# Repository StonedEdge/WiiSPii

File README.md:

# The Wii SPii (A custom GBA SP themed portable gaming console) 

## Description
The Wii SPii is an open source, portable Wii project by StonedEdge from the BitBuilt forums. It uses real Wii hardware with no emulation and lasts around 2.5 hours on a full charge. This repository includes includes code from several contributors to the hobby (Aurelio, Gmanmodz and Jefflongo), 
CAD files, gerbers for main PCB ordering and a BOM of parts for assembly. I plan to include a guide for assembly here at a later stage. The main build worklog can be found [here:](https://bitbuilt.net/forums/index.php?threads/the-wii-spii.3347/)

### Code 
The code used in this project is based on the RVL-PMS (Gman), GC+ 2.0 (Aurelio92) and STUSB4500 (jefflongo) source code from below contributors, with minor tweaks being made to suit my project needs. All credit goes to contributors and I take no credit in their work whatsoever, I simply took their contributions and made slight changes. The project code is in the form of an MPLAB X project and can be compiled using MPLAB X IDE with XC8 compiler. Alternatively, you can also use the pre-compiled program (.hex) to program the PIC16LF15324, PIC16F15324 and PIC18F25K42 with MPLAB IPE. The microcontrollers were programmed using a PICKit 3. The only code that you will need to adjust and then compile is the lines 71-74 Lmin, Lmax, Rmin and Rmax values in config.c, in order to scale the analog triggers to the correct values after reading the initial ADC values when the triggers are depressed and pressed. Code is located in the zip files. 

### CAD
The CAD files for the Wii SPii project can be found here. The case was designed with CNC manufacturing in mind and can be machined with little issue. I may include the toolpathing files at a later date, but have decided not to for now. I have uploaded both the .STEP and .STL files so that people may easily make changes to the model in their CAD software of choice, or simply print the case on any 3D printer. Prototypes were made on the Prusa i3 MK3s FDM printer and the final design was completed on a 3-axis CNC machine in acrylic plastic. I will not be taking any requests for CNC cases. 

### PCB
The PCB is a 4 layer PCB ordered from JLCPCB. The PCB can also be ordered from OSHPark or PCBway, however due to increased cost for 4-layer PCB, I would recommend ordering directly from JLCPCB for quick turnaround. A stencil is also required for ease of assembly along with solder paste and hot air to assemble the boards. I made a 3D printable stencil jig that can be used for easy placement of the stencil and PCB that I have included within the CAD zip files above. 

### BOM (Bill of Materials) 
These are the required components you will need to build the Wii SPii. This includes the PCB itself, PCB components and other peripherals required to make the console. It can be found [here:](xxx)

### Contributors 
I'd like to thank these people in no particular order for the awesome work you have done to help me complete this project. A link to their GitHub repositories can be found below. 

* Dmcke5 for helping me re-model the WiiSPii for CNC machining, CNC machining the case out of acrylic and of course the hours and hours of phone calls back and forth over the past few months. Thanks for putting up with my numerous questions on CNC
* [Gman](https://github.com/Gmanmodz) for providing the community with countless hours of research and sharing his code to allow me to make some small modifications to the LED interface and audio amplifier
* [Aurelio](https://github.com/Aurelio92) for GC+ 2.0 and BBloader Wii GUI contributions and updates
* robertlong13 for assisting in the PIC16LF15324 ADC modifications for using 10K pot for volume control over i2c
* [JeffLongo](https://github.com/jefflongo) for his STUSB4500 code revisions 
* YveltalGriffin for suggesting various hardware changes and reviews to PCB/schematics

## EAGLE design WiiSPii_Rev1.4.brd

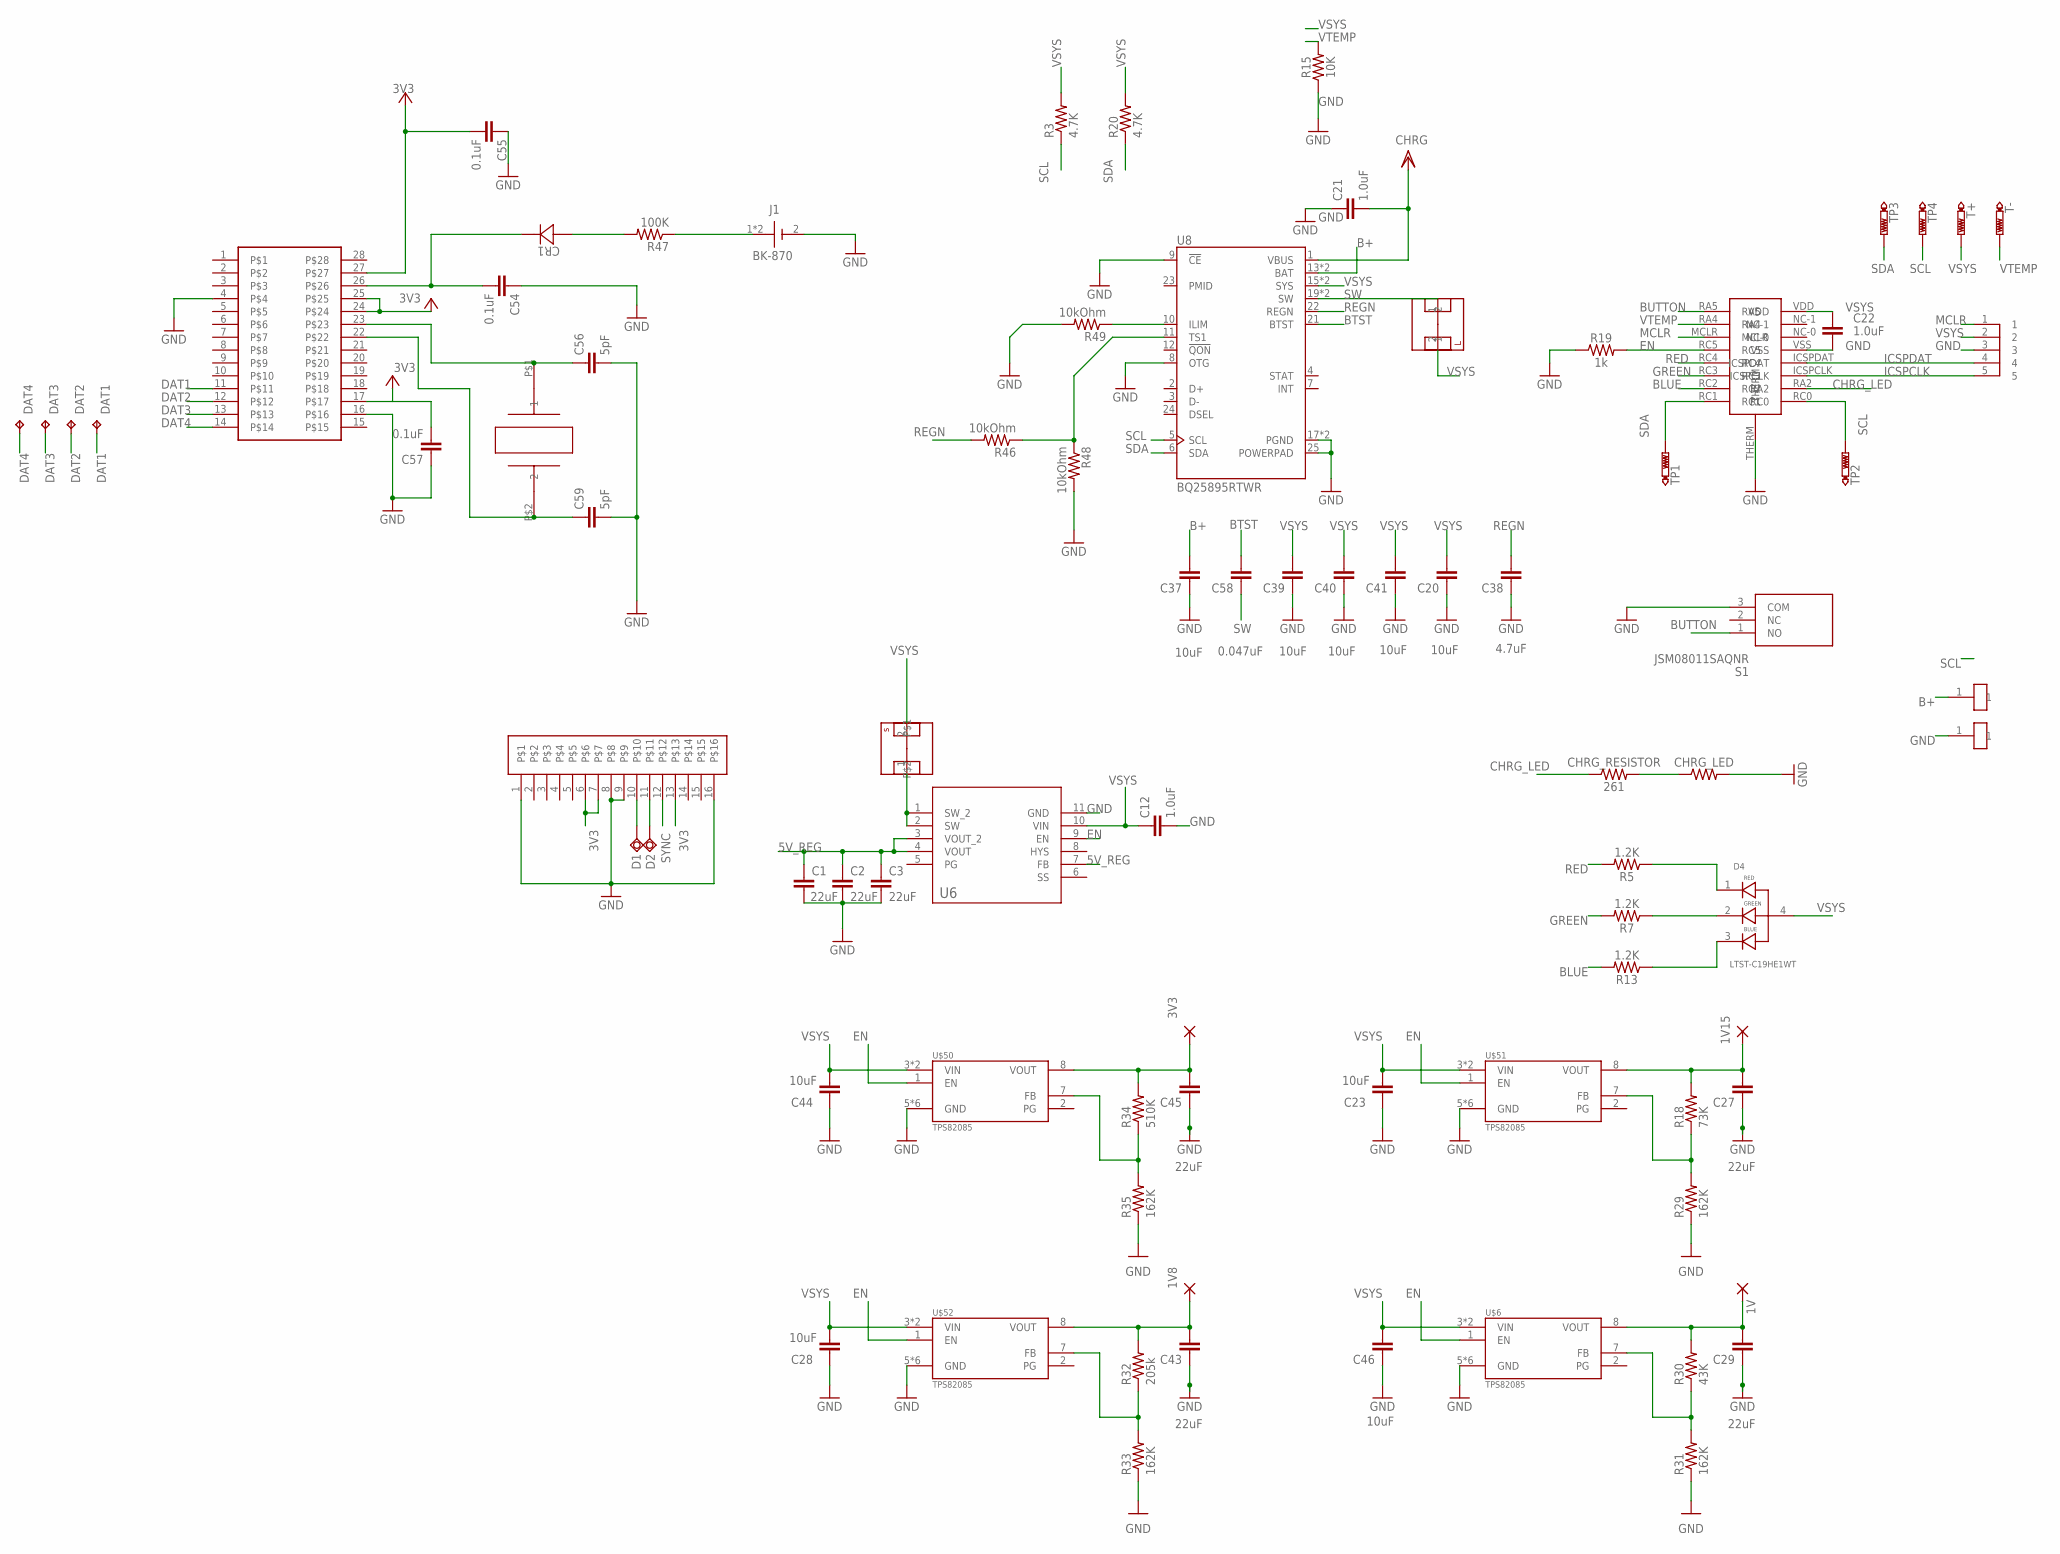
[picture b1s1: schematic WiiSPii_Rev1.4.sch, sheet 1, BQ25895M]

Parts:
1V, 1V8, 1V15, 3V3: SMD2; SMD1,27-2,54
BT_DATA1, BT_DATA2: TPSQB1,27; B1,27
C1, C2, C3, C27, C29, C43, C45: 22uF; 0805
C12, C21, C22: 1.0uF; 0805
C20, C23, C28, C37, C39, C40, C41, C44, C46: 10uF; 0805
C38: 4.7uF; C0402
C54, C55, C57: 0.1uF; C0402
C56, C59: 5pF; C0402
C58: 0.047uF; C0402
CHRG_LED: 261; 0603
CHRG_RESISTOR: 261; 0603
CR1: BAT60JFILM; SOD-323_STM
D4: LTST-C19HE1WT; LED_LTST-C19HE1WT
DAT1, DAT2, DAT3, DAT4: TPB1,27; B1,27
J1: BK-870; MPD_BK-870
R3, R20: 4.7K; R0402
R5, R7, R13: 1.2K; 0603
R15: 10K; 0603
R18: 73K; R0402
R19: 1k; 0603
R29, R31, R33, R35: 162K; R0402
R30: 43K; R0402
R32: 205k; R0402
R34: 510K; R0402
R46, R48, R49: 10kOhm; R0402
R47: 100K; R0402
S1: JSM08011SAQNR
T+: PTR1TP09R; TP09R
T-: PTR1TP09R; TP09R
TP1, TP2, TP3, TP4: PTR1TP09R; TP09R
U6: TPS61232DRCR; DRC_S-PVSON-N10
U8: BQ25895RTWR; VQFN50P400X400X100-24N
U$2: INDUCTOR_SMALL
U$6, U$50, U$51, U$52: TPS82085; SON65P280X300X133-9N
U$7: AUDIO_AMP_PIC
U$8: 1MM_PIC_PROGRAMING_HEADER; 1MM_PIC-PROGRAMING_HEADER
U$13: MOLEX_0541020164MOLEX
U$14: MX_WII
U$15: TFE20
U$27, U$28: VOLTAGE_PAD
U$49: INDUCTOR_LARGE; INDUCTOR_BIG

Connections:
1V: 1V.1, C29.2, R30.2, U$6.8 (VOUT)
1V8: 1V8.1, C43.2, R32.2, U$52.8 (VOUT); also elsewhere on the board
1V15: 1V15.1, C27.2, R18.2, U$51.8 (VOUT)
B+: C37.2, U8.13 (BAT), U8.14 (BAT), U$28.1
BLUE: R13.2, U$7.RC2
BTST: C58.2, U8.21 (BTST)
BUTTON: S1.1 (NO), U$7.RA5
CHRG: C21.2, U8.1 (VBUS); also elsewhere on the board
CHRG_LED: CHRG_RESISTOR.1, U$7.RA2
D1: BT_DATA1.TP, U$13.10
D2: BT_DATA2.TP, U$13.11
DAT1: DAT1.TP, U$14.11
DAT2: DAT2.TP, U$14.12
DAT3: DAT3.TP, U$14.13
DAT4: DAT4.TP, U$14.14
EN: R19.2, U6.9 (EN), U$6.1 (EN), U$7.RC5, U$50.1 (EN), U$51.1 (EN), U$52.1 (EN)
GND: C1.2, C2.2, C3.2, C12.2, C20.1, C21.1, C22.2, C23.1, C27.1, C28.1, C29.1, C37.1, C38.1, C39.1, C40.1, C41.1, C43.1, C44.1, C45.1, C46.1, C54.1, C55.1, C56.2, C57.1, C59.2, CHRG_LED.2, J1.2 (M), R15.1, R19.1, R29.1, R31.1, R33.1, R35.1, R48.2, R49.2, S1.3 (COM), U6.11 (GND), U8.8 (OTG), U8.9 (!CE), U8.17 (PGND), U8.18 (PGND), U8.25 (POWERPAD), U$6.5 (GND), U$6.6 (GND), U$6.9 (GND), U$6.P$1 (GND), U$6.P$2 (GND), U$6.P$3 (GND), U$7.THERM, U$7.VSS, U$8.3, U$13.1, U$13.8, U$13.9, U$13.16, U$14.4, U$14.16, U$27.1, U$50.5 (GND), U$50.6 (GND), U$50.9 (GND), U$50.P$1 (GND), U$50.P$2 (GND), U$50.P$3 (GND), U$51.5 (GND), U$51.6 (GND), U$51.9 (GND), U$51.P$1 (GND), U$51.P$2 (GND), U$51.P$3 (GND), U$52.5 (GND), U$52.6 (GND), U$52.9 (GND), U$52.P$1 (GND), U$52.P$2 (GND), U$52.P$3 (GND); also elsewhere on the board
GREEN: R7.2, U$7.RC3
ICSPCLK: U$7.ICSPCLK, U$8.5
ICSPDAT: U$7.ICSPDAT, U$8.4
MCLR: U$7.MCLR, U$8.1
unnamed: U6.1 (SW_2), U6.2 (SW), U$2.1
unnamed: D4.2, R7.1
unnamed: D4.1, R5.1
unnamed: D4.3, R13.1
unnamed: CHRG_LED.1, CHRG_RESISTOR.2
unnamed: C56.1, U$14.23, U$15.P$1 (1)
unnamed: C59.1, U$14.22, U$15.P$2 (2)
unnamed: CR1.2, R47.2
unnamed: R18.1, R29.2, U$51.7 (FB)
unnamed: R46.1, R48.1, U8.11 (TS1)
unnamed: R49.1, U8.10 (ILIM)
unnamed: C54.2, CR1.1, U$14.26
unnamed: J1.1, J1.3, R47.1
unnamed: R30.1, R31.2, U$6.7 (FB)
unnamed: R32.1, R33.2, U$52.7 (FB)
unnamed: R34.1, R35.2, U$50.7 (FB)
RED: R5.2, U$7.RC4
REGN: C38.2, R46.2, U8.22 (REGN)
SCL: R3.1, TP2.TP, TP4.TP, U8.5 (SCL), U$7.RC0; also elsewhere on the board
SDA: R20.1, TP1.TP, TP3.TP, U8.6 (SDA), U$7.RC1; also elsewhere on the board
SW: C58.1, U8.19 (SW), U8.20 (SW), U$49.1
SYNC: U$13.12; also elsewhere on the board
VSYS: C12.1, C20.2, C22.1, C23.2, C28.2, C39.2, C40.2, C41.2, C44.2, C46.2, D4.4, R3.2, R20.2, T+.TP, U6.10 (VIN), U8.15 (SYS), U8.16 (SYS), U$2.2, U$6.3 (VIN), U$6.4 (VIN), U$7.VDD, U$8.2, U$49.2, U$50.3 (VIN), U$50.4 (VIN), U$51.3 (VIN), U$51.4 (VIN), U$52.3 (VIN), U$52.4 (VIN); also elsewhere on the board
VTEMP: R15.2, T-.TP, U$7.RA4

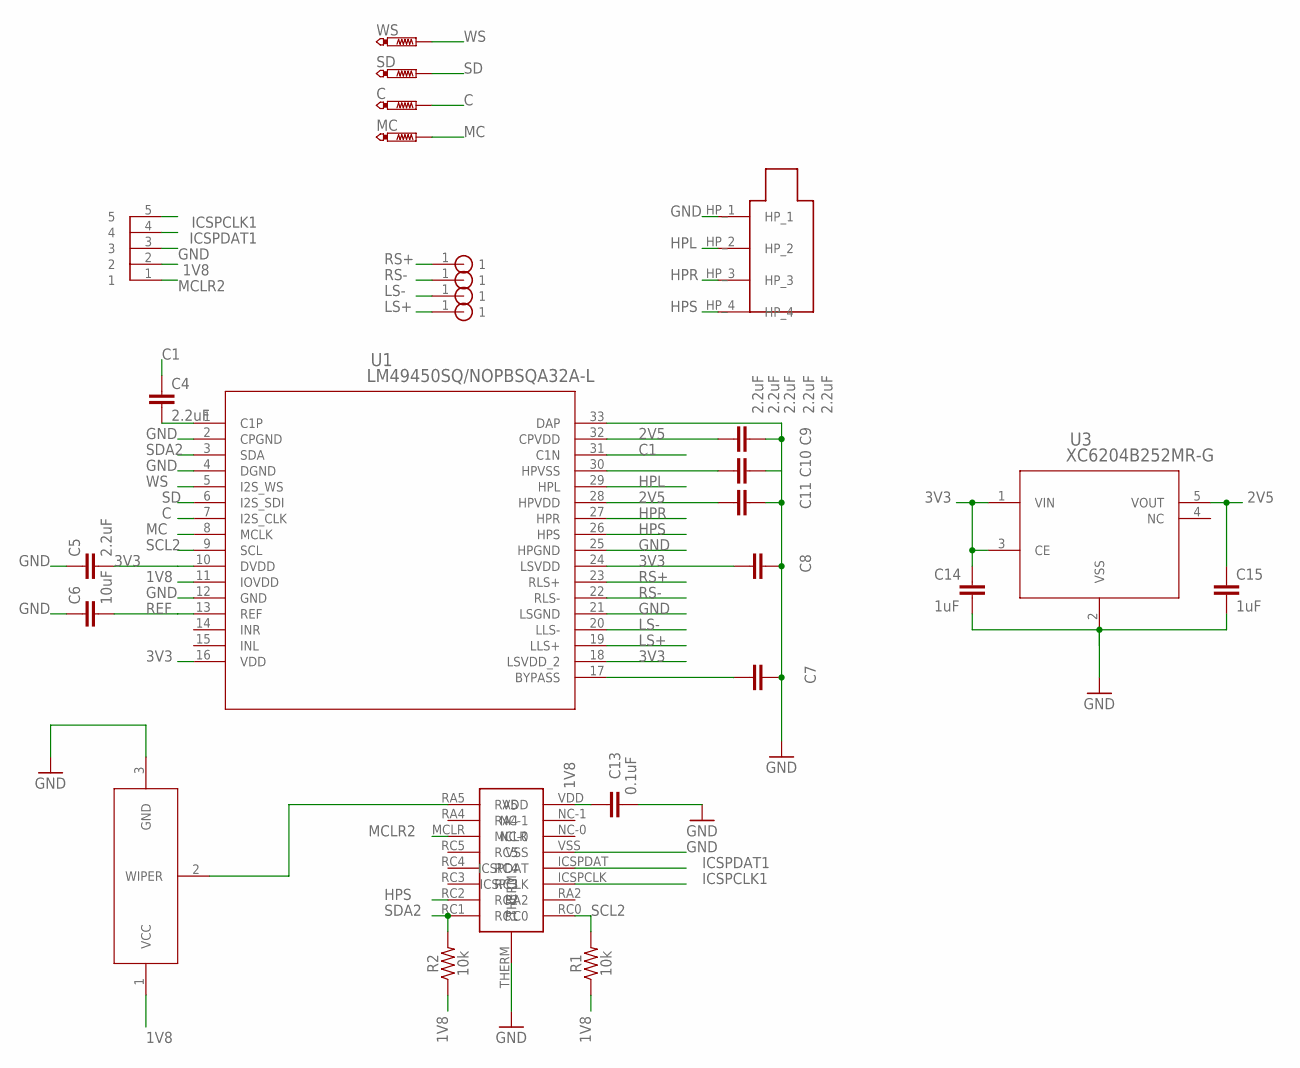
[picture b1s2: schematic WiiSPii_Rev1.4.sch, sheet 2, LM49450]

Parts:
C: PTR1TP09R; TP09R
C4, C5, C7, C8, C9, C10, C11: 2.2uF; 0603
C6: 10uF; 0603
C13: 0.1uF; 0603
C14, C15: 1uF; 0603
MC: PTR1TP09R; TP09R
R1, R2: 10k; 0603
RS+: WII_VIA
SD: PTR1TP09R; TP09R
U1: LM49450SQ/NOPBSQA32A-L; SQA32A-L
U3: XC6204B252MR-G; XC6204/05_SOT-25
U$1: AUDIO_AMP_PIC
U$3: 1MM_PIC_PROGRAMING_HEADER; 1MM_PIC-PROGRAMING_HEADER
U$9: RK10J11R001Y
U$40, U$41, U$42: WII_VIA
U$44: HP_JACK
WS: PTR1TP09R; TP09R

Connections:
1V8: C13.1, R1.1, R2.1, U1.11 (IOVDD), U$1.VDD, U$3.2, U$9.1 (VCC); also elsewhere on the board
2V5: C9.1, C11.1, C15.1, U1.28 (HPVDD), U1.32 (CPVDD), U3.5 (VOUT)
C: C.TP, U1.7 (I2S_CLK)
C1: C4.1, U1.31 (C1N)
GND: C5.1, C6.1, C7.1, C8.1, C9.2, C10.2, C11.2, C13.2, C14.2, C15.2, U1.2 (CPGND), U1.4 (DGND), U1.12 (GND), U1.21 (LSGND), U1.25 (HPGND), U1.33 (DAP), U3.2 (VSS), U$1.THERM, U$1.VSS, U$3.3, U$9.3 (GND), U$44.HP_1; also elsewhere on the board
HPL: U1.29 (HPL), U$44.HP_2
HPR: U1.27 (HPR), U$44.HP_3
HPS: U1.26 (HPS), U$1.RC2, U$44.HP_4
ICSPCLK1: U$1.ICSPCLK, U$3.5
ICSPDAT1: U$1.ICSPDAT, U$3.4
LS+: U1.19 (LLS+), U$42.1
LS-: U1.20 (LLS-), U$41.1
MC: MC.TP, U1.8 (MCLK)
MCLR2: U$1.MCLR, U$3.1
unnamed: C7.2, U1.17 (BYPASS)
unnamed: C10.1, U1.30 (HPVSS)
unnamed: U$1.RA5, U$9.2 (WIPER)
PIN1: C4.2, U1.1 (C1P)
REF: C6.2, U1.13 (REF)
RS+: RS+.1, U1.23 (RLS+)
RS-: U1.22 (RLS-), U$40.1
SCL2: R1.2, U1.9 (SCL), U$1.RC0
SD: SD.TP, U1.6 (I2S_SDI)
SDA2: R2.2, U1.3 (SDA), U$1.RC1
WS: U1.5 (I2S_WS), WS.TP

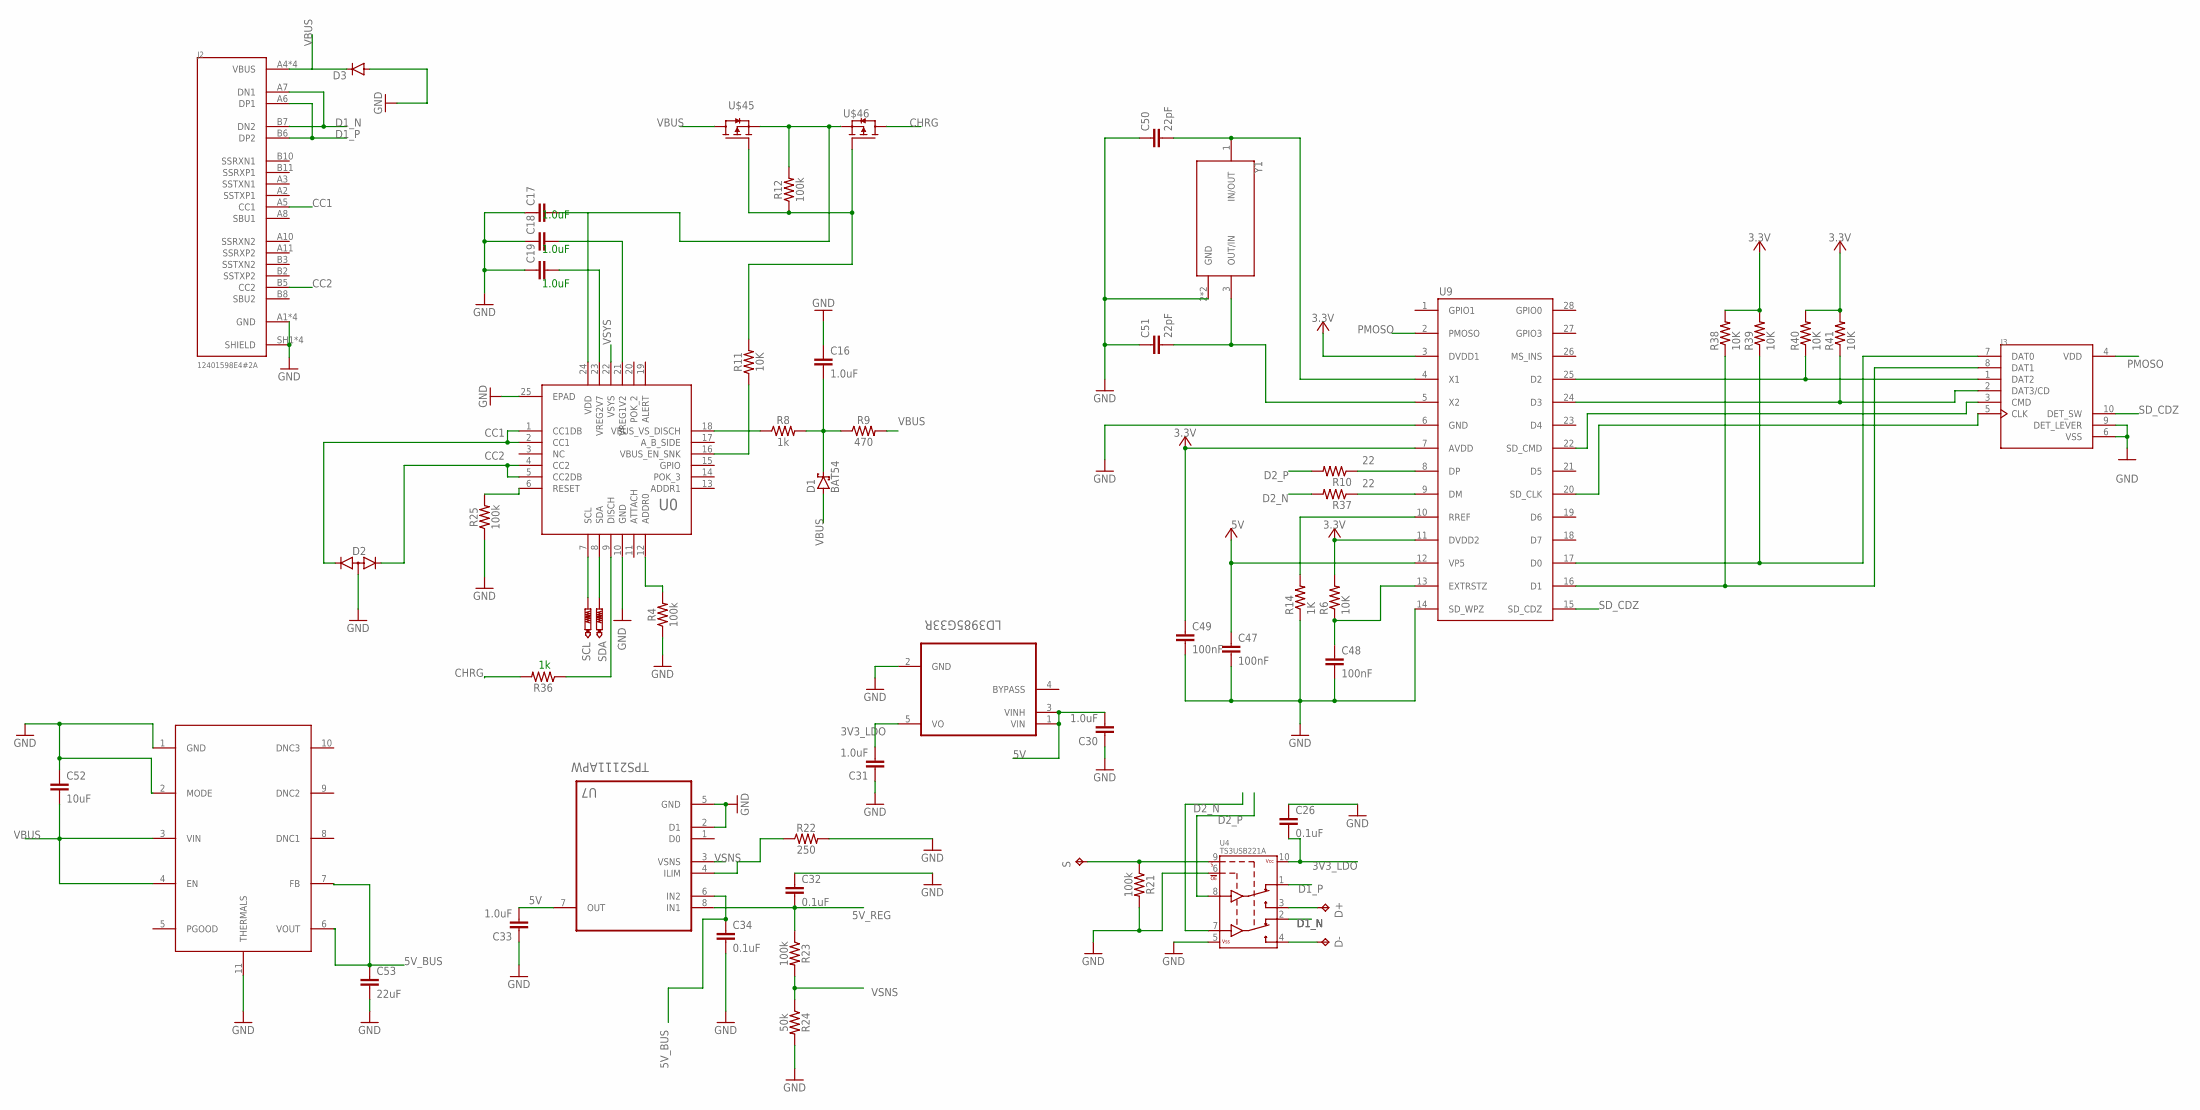
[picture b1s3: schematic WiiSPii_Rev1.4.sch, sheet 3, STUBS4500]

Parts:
C16, C17, C18, C19, C30, C31, C33: 1.0uF; 0603
C26, C32, C34: 0.1uF; 0603
C47, C48, C49: 100nF; C0402
C50, C51: 22pF; C0402
C52: 10uF; 1210
C53: 22uF; 1210
D1: BAT54; SOT23
D2: ESDA25W; SOT65P210X110-3N
D3: ESDA25P35-1U1M; ESDA8P801U1M
D+: TPB1,27; B1,27
D-: TPB1,27; B1,27
J2: 12401598E4#2A; AMPHENOL_12401598E4#2A
J3: 5025700893; MOLEX_5025700893
R4, R12, R21, R23, R25: 100k; 0603
R6, R38, R39, R40, R41: 10K; R0402
R8: 1k; 0603
R9: 470; 0603
R10, R37: 22; R0402
R11: 10K; 0603
R14: 1K; R0402
R22: 250; 0603
R24: 50k; 0603
R36: 1K; 0603
S: TPB1,27; B1,27
SCL: PTR1TP09R; TP09R
SDA: PTR1TP09R; TP09R
U0: STUSB4500; QFN50P440X440X100-25T255
U4: TS3USB221A; QFN-10-RSE
U5: LD3985G33R; SOT95P280X145-5N
U7: TPS2111APW; SOP65P640X120-8N
U9: GL82L_SSOP; GL827L_SSOP
U$10: LMZM23601; MODULE_LMZM23600SILR
U$45, U$46: STL6P3LLH6; POWERFLAT_3.3X3.3
Y1: ECS-120-13-30B-AEM-TR; XTAL_ECS-120-13-30B-AEM-TR

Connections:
3.3V: C49.1, R6.2, R38.2, R39.2, R40.2, R41.2, U9.3 (DVDD1), U9.7 (AVDD), U9.11 (DVDD2)
3V3_LDO: C26.2, C31.2, U4.10 (VCC), U5.5 (VO)
5V: C30.2, C33.2, C47.1, U5.1 (VIN), U5.3 (VINH), U7.7 (OUT), U9.12 (VP5)
5V_BUS: C34.1, C53.1, U7.6 (IN2), U$10.6 (VOUT), U$10.7 (FB)
CC1: D2.1 (K2), J2.A5 (CC1), U0.1 (CC1DB), U0.2 (CC1)
CC2: D2.2 (K1), J2.B5 (CC2), U0.4 (CC2), U0.5 (CC2DB)
CHRG: R36.2, U$46.5 (D), U$46.6 (D), U$46.7 (D); also elsewhere on the board
D1_N: J2.A7 (DN1), J2.B7 (DN2), U4.2 (1D-)
D1_P: J2.A6 (DP1), J2.B6 (DP2), U4.1 (1D+)
D2_N: R37.2, U4.7 (D-)
D2_P: R10.2, U4.8 (D+)
GND: C16.1, C17.1, C18.1, C19.1, C26.1, C30.1, C31.1, C32.1, C33.1, C34.2, C47.2, C48.2, C49.2, C50.1, C51.1, C52.1, C53.2, D2.3 (A), D3.1 (A), J2.A1 (GND), J2.A12 (GND), J2.B1 (GND), J2.B12 (GND), J2.SH1 (SHIELD), J2.SH2 (SHIELD), J2.SH3 (SHIELD), J2.SH4 (SHIELD), J3.6 (VSS), J3.9 (DET_LEVER), R4.1, R14.1, R21.2, R22.2, R24.2, R25.1, U0.10 (GND), U0.25 (EPAD), U4.5 (VSS), U4.6 (!OE), U5.2 (GND), U7.2 (D1), U7.5 (GND), U9.6 (GND), U9.14 (SD_WPZ), U$10.1 (GND), U$10.2 (MODE), U$10.11 (THERMALS), Y1.2 (GND), Y1.4 (GND); also elsewhere on the board
unnamed: R4.2, U0.12 (ADDR0)
unnamed: R8.1, U0.18 (VBUS_VS_DISCH)
unnamed: C19.2, U0.23 (VREG2V7)
unnamed: R11.1, U0.16 (VBUS_EN_SNK)
unnamed: R11.2, R12.1, U$45.4 (G), U$46.4 (G)
unnamed: R36.1, U0.9 (DISCH)
unnamed: D-.TP, U4.4 (2D-)
unnamed: D+.TP, U4.3 (2D+)
unnamed: R22.1, U7.4 (ILIM)
unnamed: R25.2, U0.6 (RESET)
unnamed: C18.2, U0.21 (VREG1V2)
unnamed: C16.2, D1.3 (C), R8.2, R9.1
unnamed: C48.1, R6.1, U9.13 (EXTRSTZ)
unnamed: R14.2, U9.10 (RREF)
unnamed: R10.1, U9.8 (DP)
unnamed: R37.1, U9.9 (DM)
unnamed: C50.2, U9.4 (X1), Y1.1 (IN/OUT)
unnamed: J3.1 (DAT2), R40.1, U9.25 (D2)
unnamed: J3.2 (DAT3/CD), R41.1, U9.24 (D3)
unnamed: J3.3 (CMD), U9.22 (SD_CMD)
unnamed: J3.5 (CLK), U9.20 (SD_CLK)
unnamed: J3.8 (DAT1), R38.1, U9.16 (D1)
unnamed: J3.7 (DAT0), R39.1, U9.17 (D0)
unnamed: C51.2, U9.5 (X2), Y1.3 (OUT/IN)
PMOSO: J3.4 (VDD), U9.2 (PMOSO)
SCL: SCL.TP, U0.7 (SCL); also elsewhere on the board
SDA: SDA.TP, U0.8 (SDA); also elsewhere on the board
SD_CDZ: J3.10 (DET_SW), U9.15 (SD_CDZ)
VBUS: C52.2, D1.1 (A), D3.2 (C), J2.A4 (VBUS), J2.A9 (VBUS), J2.B4 (VBUS), J2.B9 (VBUS), R9.2, U$10.3 (VIN), U$10.4 (EN), U$45.5 (D), U$45.6 (D), U$45.7 (D)
VCC: C17.2, R12.2, U0.24 (VDD), U$45.1 (S), U$45.2 (S), U$45.3 (S), U$46.1 (S), U$46.2 (S), U$46.3 (S)
VSNS: R23.2, R24.1, U7.3 (VSNS)
VSYS: U0.22 (VSYS); also elsewhere on the board

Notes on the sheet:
1.0uF

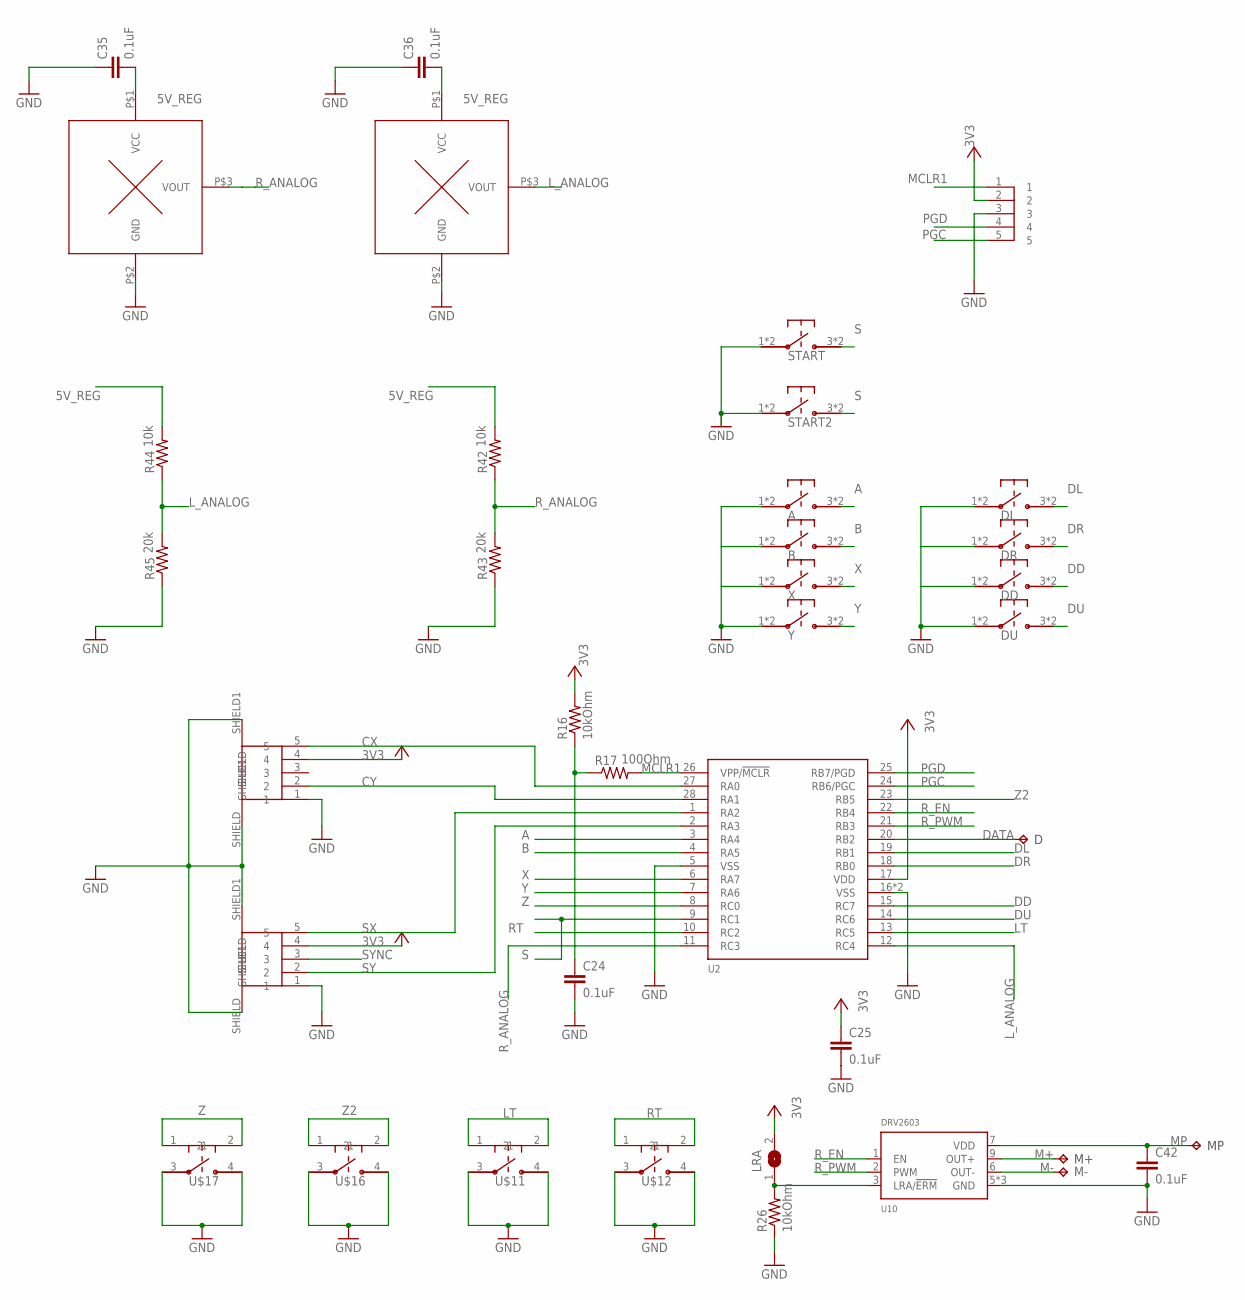
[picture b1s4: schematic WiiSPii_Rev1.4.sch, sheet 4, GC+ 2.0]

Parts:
A: TL3315NF100Q
B: TL3315NF100Q
C24, C25, C35, C36, C42: 0.1uF; C0402
DATA: TPTP10SQ; TP10SQ
DD: TL3315NF100Q
DL: TL3315NF100Q
DR: TL3315NF100Q
DU: TL3315NF100Q
HS1, HS2: MLX90290
LRA: SJ
M+: TPTP10SQ; TP10SQ
M-: TPTP10SQ; TP10SQ
MP: TPTP10SQ; TP10SQ
R16, R26: 10kOhm; R0402
R17: 100Ohm; R0402
R42, R44: 10k; R0402
R43, R45: 20k; R0402
START, START2: TL3315NF100Q
U2: PIC18F25K42; QFN-28
U10: DRV2603; WQFN-10
U$4, U$5: SWITCHSTICK_BREAKOUT
U$11, U$12, U$16, U$17: EVQ-P7J01P
U$18: 1MM_PIC_PROGRAMING_HEADER; 1MM_PIC-PROGRAMING_HEADER
X: TL3315NF100Q
Y: TL3315NF100Q

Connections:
A: A.3, A.4, U2.3 (RA4)
B: B.3, B.4, U2.4 (RA5)
CX: U2.27 (RA0), U$5.5
CY: U2.28 (RA1), U$5.2
DD: DD.3, DD.4, U2.15 (RC7)
DL: DL.3, DL.4, U2.19 (RB1)
DR: DR.3, DR.4, U2.18 (RB0)
DU: DU.3, DU.4, U2.14 (RC6)
GND: A.1, A.2, B.1, B.2, C24.2, C25.2, C35.1, C36.1, C42.2, DD.1, DD.2, DL.1, DL.2, DR.1, DR.2, DU.1, DU.2, HS1.P$2 (GND), HS2.P$2 (GND), R26.1, R43.1, R45.1, START.1, START.2, START2.1, START2.2, U2.5 (VSS), U2.16 (VSS), U10.5 (GND), U10.8 (GND), U10.10 (GND), U$4.1, U$4.SHIELD, U$4.SHIELD1, U$5.1, U$5.SHIELD, U$5.SHIELD1, U$11.3, U$11.4, U$12.3, U$12.4, U$16.3, U$16.4, U$17.3, U$17.4, U$18.3, X.1, X.2, Y.1, Y.2; also elsewhere on the board
LT: U2.13 (RC5), U$11.1, U$11.2
M+: M+.TP, U10.9 (OUT+)
M-: M-.TP, U10.6 (OUT-)
MCLR1: R17.2, U2.26 (VPP/!MCLR), U$18.1
MP: C42.1, MP.TP, U10.7 (VDD)
unnamed: LRA.1, R26.2, U10.3 (LRA/!ERM)
unnamed: DATA.TP, U2.20 (RB2)
unnamed: C24.1, R16.1, R17.1
PGC: U2.24 (RB6/PGC), U$18.5
PGD: U2.25 (RB7/PGD), U$18.4
RT: U2.10 (RC2), U$12.1, U$12.2
R_EN: U2.22 (RB4), U10.1 (EN)
R_PWM: U2.21 (RB3), U10.2 (PWM)
S: START.3, START.4, START2.3, START2.4, U2.9 (RC1)
SX: U2.1 (RA2), U$4.5
SY: U2.2 (RA3), U$4.2
SYNC: U$4.3; also elsewhere on the board
X: U2.6 (RA7), X.3, X.4
Y: U2.7 (RA6), Y.3, Y.4
Z: U2.8 (RC0), U$17.1, U$17.2
Z2: U2.23 (RB5), U$16.1, U$16.2

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
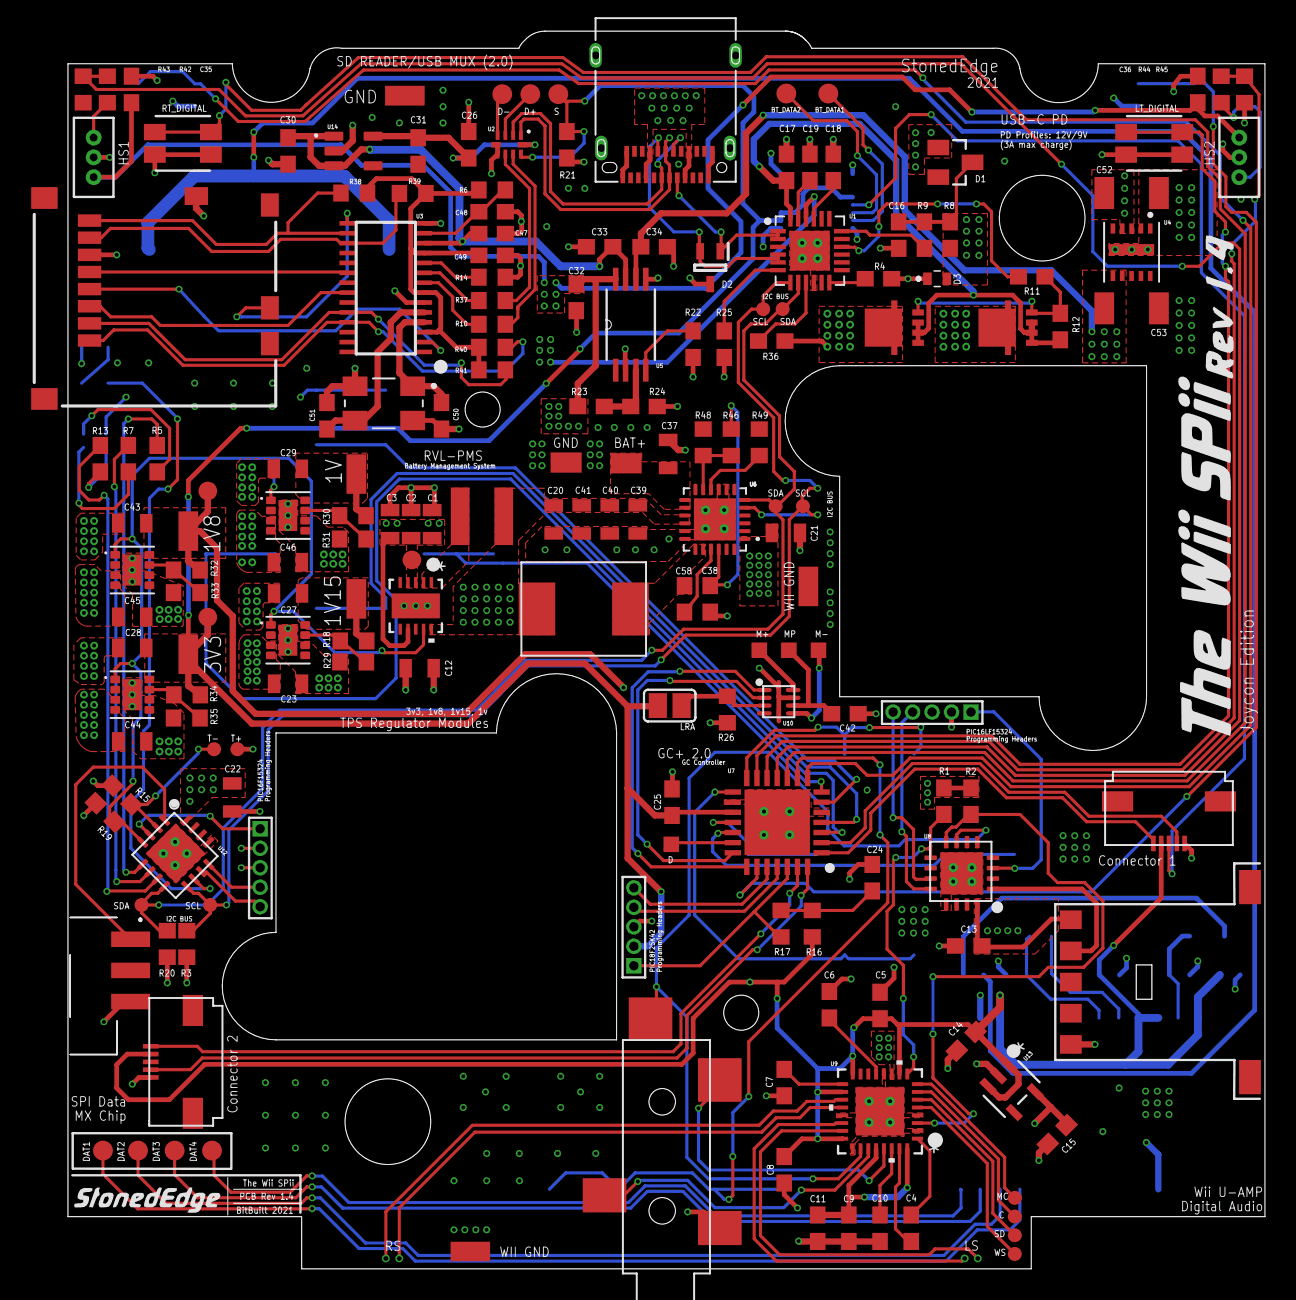
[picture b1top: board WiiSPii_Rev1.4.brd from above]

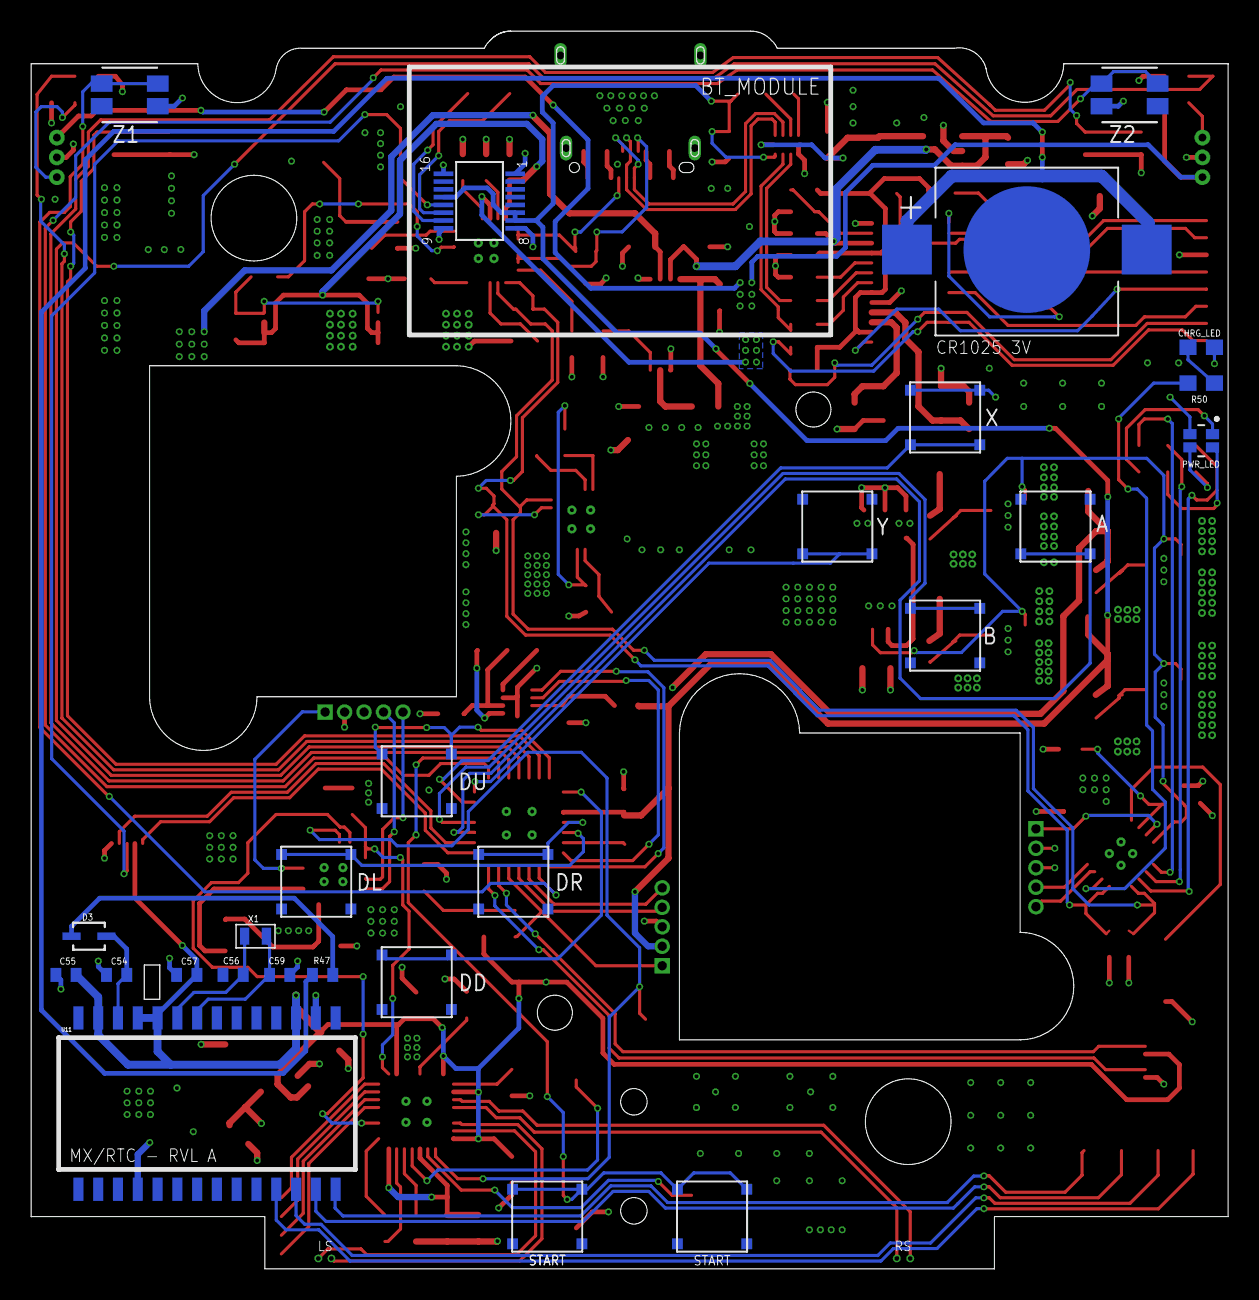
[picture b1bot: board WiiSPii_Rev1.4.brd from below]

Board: 4 copper layers, 76.8 x 79.4 mm, 208 parts (27 on the bottom side), 141 nets.

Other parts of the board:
3V3_SCREEN: PTR1TP12R; TP12R
GND: SMD1,27-2,54
GND(WII), GND(WII)1: SMD1,27-2,54
TP6, TP7: PTR1TP12R; TP12R

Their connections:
1V8: TP6.TP; also elsewhere on the board
GND: GND.1, GND(WII).1, GND(WII)1.1; also elsewhere on the board

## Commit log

2024-06-08 Restructure source code directory
2026-05-30 Upload old ass files for archive purposes (inconsistent schematics, cant find 1.4 sch).

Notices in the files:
parts and their libraries:
SparkFun-Capacitors: Licensing: Creative Commons ShareAlike 4.0 International - https://creativecommons.org/licenses/by-sa/4.0
COPYRIGHT: Copyright (C) 2018 Accelerated Designs. All rights reserved
